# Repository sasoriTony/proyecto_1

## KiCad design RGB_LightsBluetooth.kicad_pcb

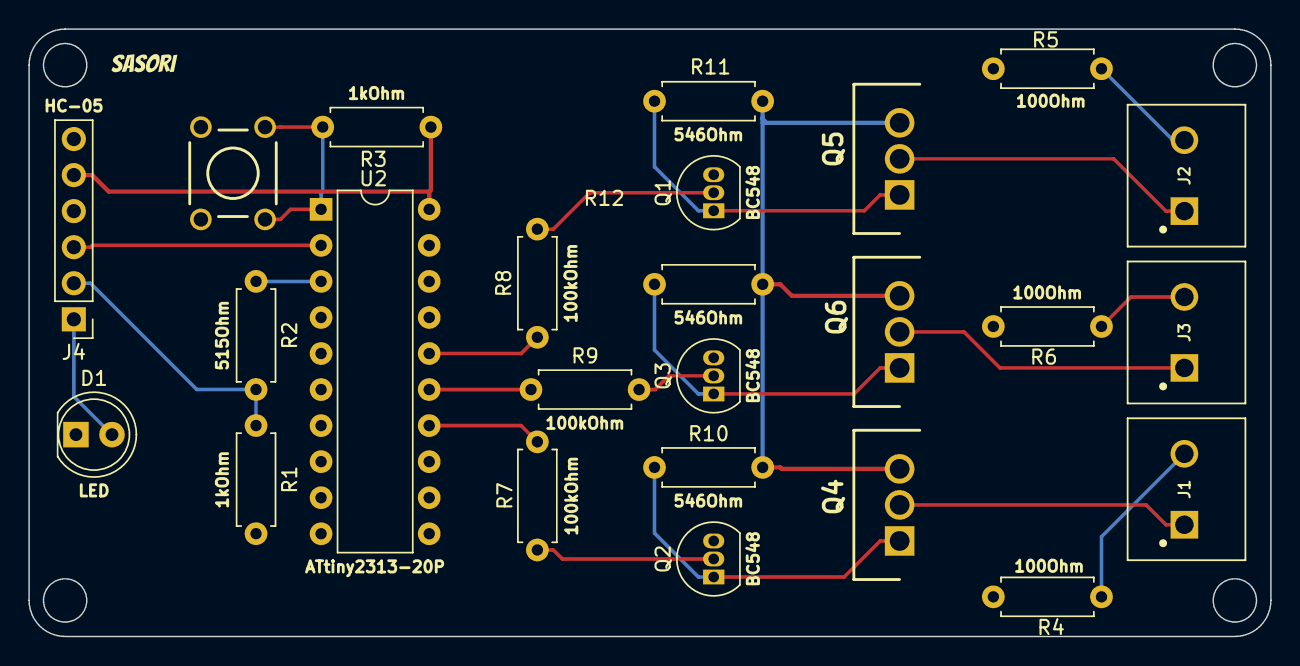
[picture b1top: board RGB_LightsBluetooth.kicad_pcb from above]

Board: 2 copper layers, 87.5 x 42.8 mm, 25 parts (0 on the bottom side), 23 nets.

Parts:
D1: LED; LED_D5.0mm
J1, J2, J3: 1935161; PHOENIX_1935161
J4: HC-05; PinHeader_1x06_P2.54mm_Vertical
Q1, Q2, Q3: BC548; TO-92_Inline
Q4, Q5, Q6: IRF9640; TO254P465X1024X2050-3P
R1, R3: 1kOhm; R_Axial_DIN0207_L6.3mm_D2.5mm_P7.62mm_Horizontal
R2: 515Ohm; R_Axial_DIN0207_L6.3mm_D2.5mm_P7.62mm_Horizontal
R4, R5, R6: 100Ohm; R_Axial_DIN0207_L6.3mm_D2.5mm_P7.62mm_Horizontal
R7, R8, R9: 100kOhm; R_Axial_DIN0207_L6.3mm_D2.5mm_P7.62mm_Horizontal
R10, R11, R12: 546Ohm; R_Axial_DIN0207_L6.3mm_D2.5mm_P7.62mm_Horizontal
SW1: SW_DPST; SW_PUSHBUTTON_PTH
U2: ATtiny2313-20P; DIP-20_W7.62mm

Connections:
/5V: J4.5, R3.1, U2.20 (VCC)
/12V: Q4.3, Q5.3, Q6.3, R10.2, R11.2, R12.2
/B: R8.1, U2.16 (PB4)
/G: R9.1, U2.15 (PB3)
/R: R7.1, U2.14 (PB2)
/RX: J4.3, U2.2 (PD0)
/TX: J4.2, R1.1, R2.2
GND: D1.1 (K), J4.4, Q1.3 (E), Q2.3 (E), Q3.3 (E), R1.2, R4.2, R5.2, R6.2, SW1.1, U2.10 (GND)
unnamed: D1.2 (A), J4.1
unnamed: J1.1, Q4.2
unnamed: J1.2, R4.1
unnamed: J2.1, Q5.2
unnamed: J2.2, R5.1
unnamed: J3.1, Q6.2
unnamed: J3.2, R6.1
unnamed: Q1.1 (C), Q5.1, R11.1
unnamed: Q1.2 (B), R8.2
unnamed: Q2.1 (C), Q4.1, R10.1
unnamed: Q2.2 (B), R7.2
unnamed: Q3.1 (C), Q6.1, R12.1
unnamed: Q3.2 (B), R9.2
unnamed: R2.1, U2.3 (PD1)
unnamed: R3.2, SW1.2, U2.1 (PA2/~RESET)

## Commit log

2022-05-05 pcb without route
2022-05-05 pcb autorouting
2022-05-06 pcb autorouting version 1
2022-05-06 nuevo
2022-05-06 pcb routing version 2
2022-05-06 resolviendo problema
2022-05-06 pcb autorouting version 3
2022-05-06 pista corregida
